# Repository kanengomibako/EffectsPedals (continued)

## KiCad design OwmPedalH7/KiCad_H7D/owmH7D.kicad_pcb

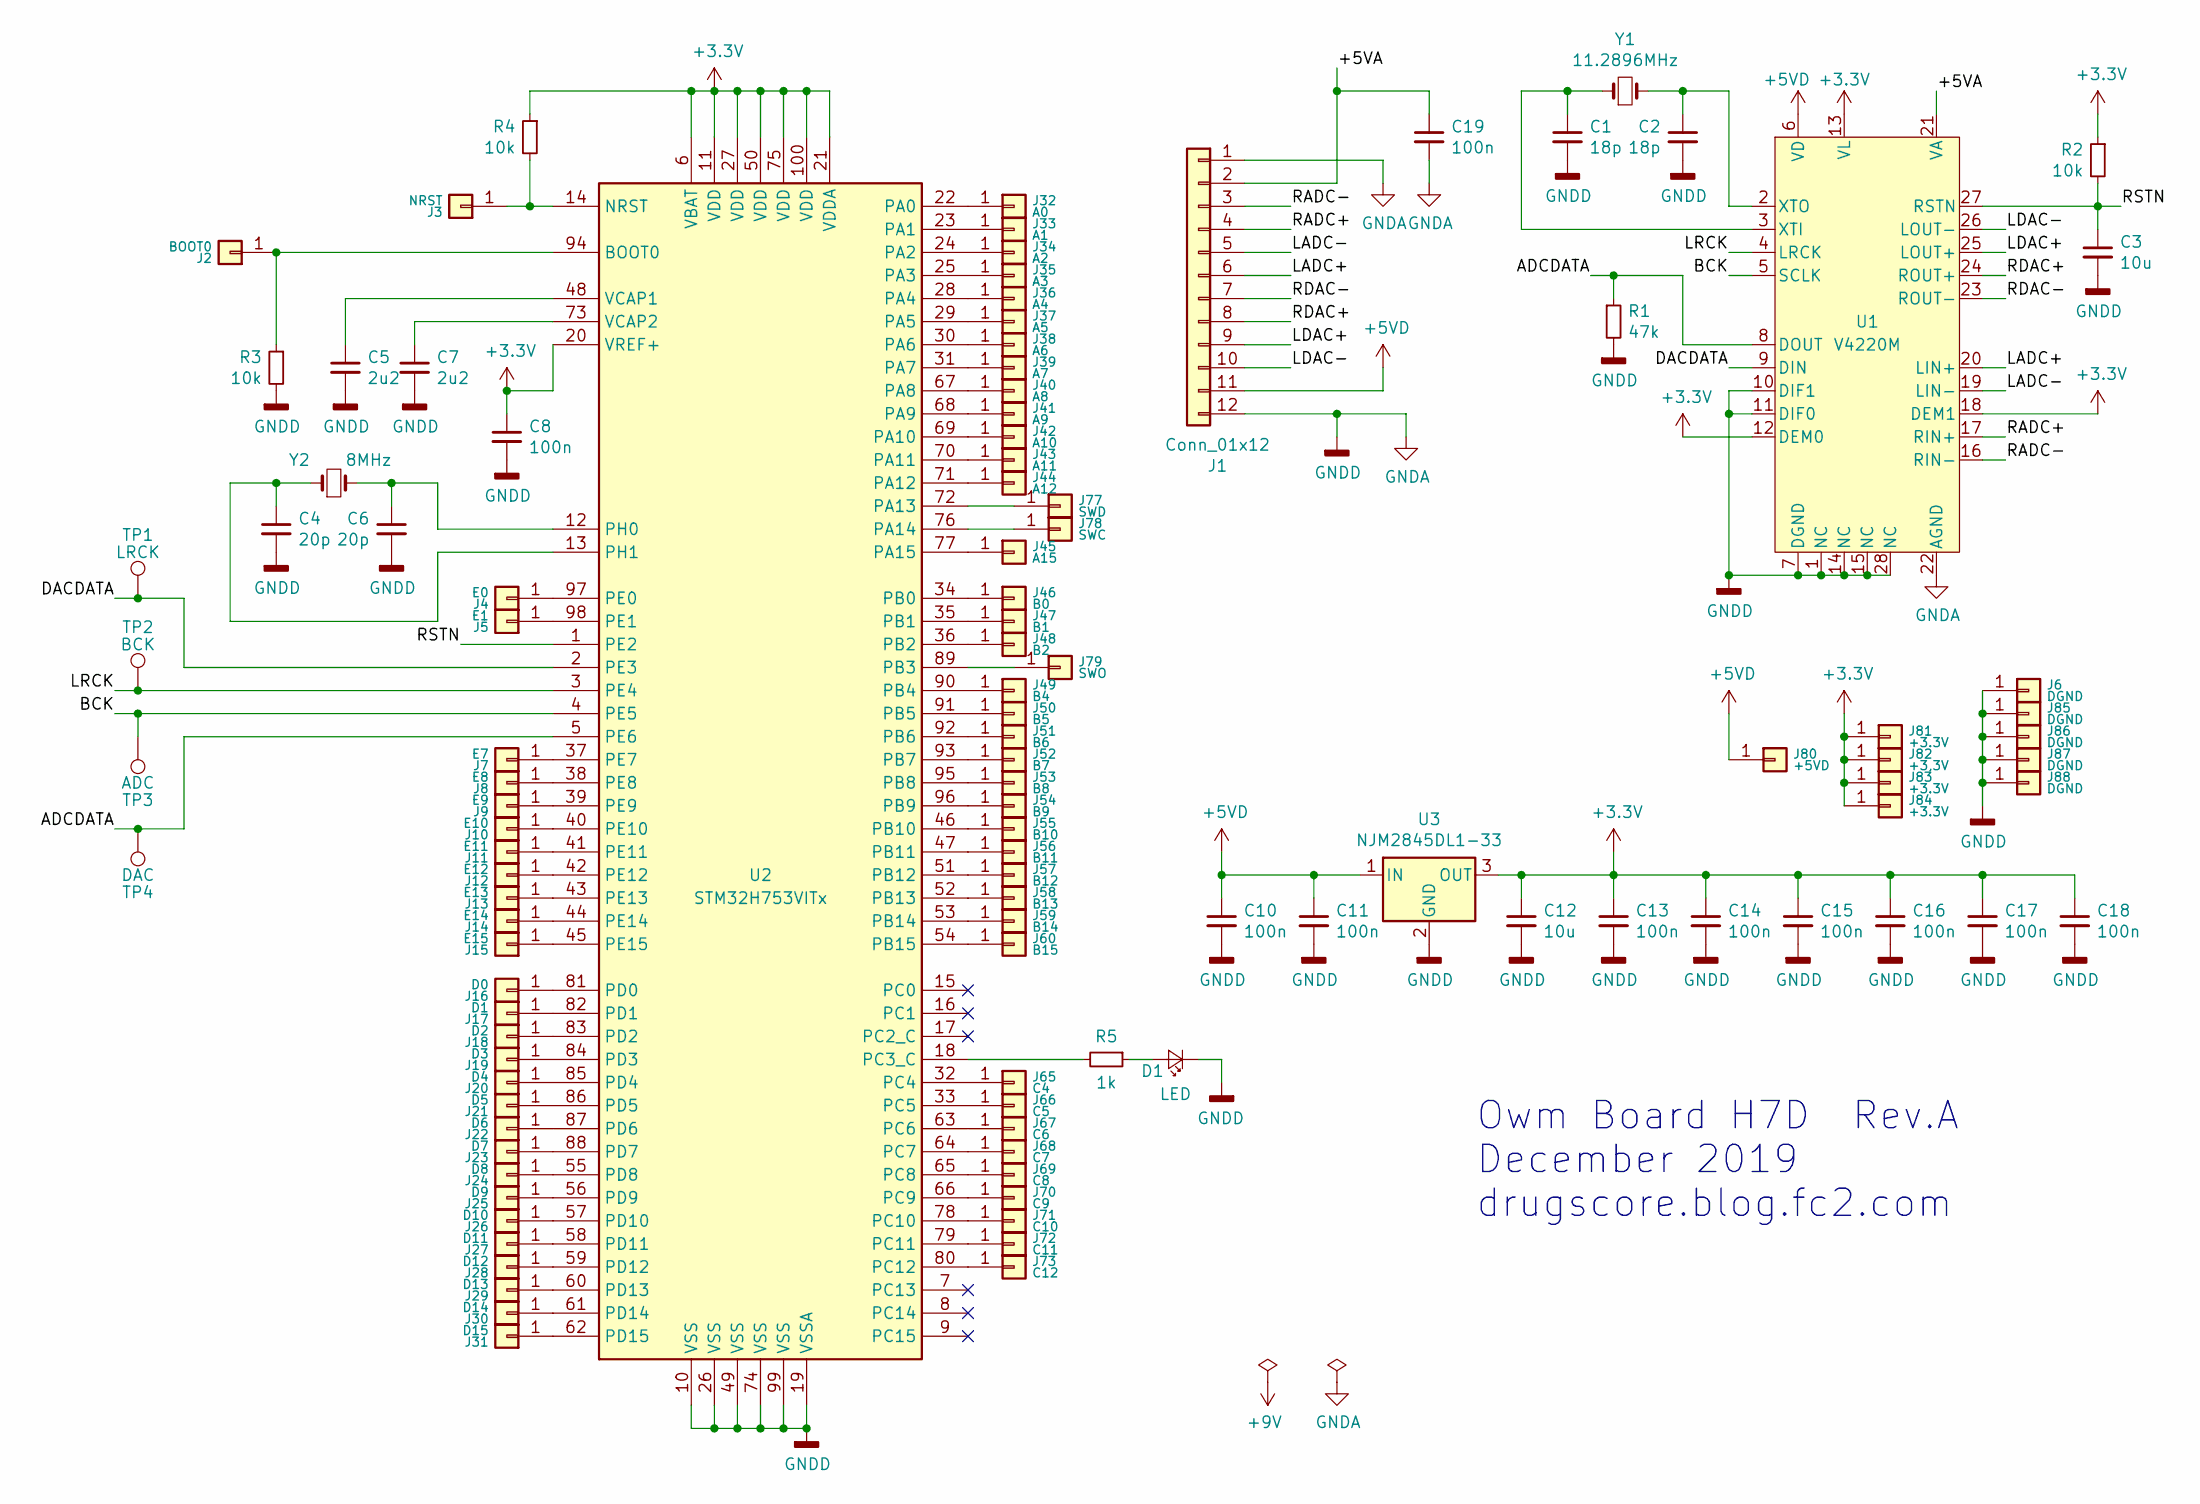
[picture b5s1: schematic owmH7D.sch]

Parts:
C1, C2: 18p; my_C_1608(0603)_HandSoldering
C3, C12: 10u; my_C_3216(1206)_HandSoldering
C4, C6: 20p; my_C_1608(0603)_HandSoldering
C5, C7: 2u2; my_C_2012(0805)_HandSoldering
C8, C10, C11, C13, C14, C15, C16, C17, C18, C19: 100n; my_C_1608(0603)_HandSoldering
D1: LED; my_R_1608(0603)_HandSoldering
J1: Conn_01x12; PinHeader_1x12_P2.54mm_Vertical
J2: BOOT0; my_SmallPad_0-8mmDrill
J3: NRST; my_SmallPad_0-8mmDrill
J4: E0; my_SmallPad_0-8mmDrill
J5: E1; my_SmallPad_0-8mmDrill
J6, J85, J86, J87, J88: DGND; my_SmallPad_0-8mmDrill
J7: E7; my_SmallestPad_0-6mmDrill
J8: E8; my_SmallestPad_0-6mmDrill
J9: E9; my_SmallestPad_0-6mmDrill
J10: E10; my_SmallestPad_0-6mmDrill
J11: E11; my_SmallestPad_0-6mmDrill
J12: E12; my_SmallestPad_0-6mmDrill
J13: E13; my_SmallestPad_0-6mmDrill
J14: E14; my_SmallestPad_0-6mmDrill
J15: E15; my_SmallestPad_0-6mmDrill
J16: D0; my_SmallestPad_0-6mmDrill
J17: D1; my_SmallestPad_0-6mmDrill
J18: D2; my_SmallestPad_0-6mmDrill
J19: D3; my_SmallestPad_0-6mmDrill
J20: D4; my_SmallestPad_0-6mmDrill
J21: D5; my_SmallestPad_0-6mmDrill
J22: D6; my_SmallestPad_0-6mmDrill
J23: D7; my_SmallestPad_0-6mmDrill
J24: D8; my_SmallPad_0-8mmDrill
J25: D9; my_SmallPad_0-8mmDrill
J26: D10; my_SmallPad_0-8mmDrill
J27: D11; my_SmallPad_0-8mmDrill
J28: D12; my_SmallPad_0-8mmDrill
J29: D13; my_SmallestPad_0-6mmDrill
J30: D14; my_SmallestPad_0-6mmDrill
J31: D15; my_SmallestPad_0-6mmDrill
J32: A0; my_SmallPad_0-8mmDrill
J33: A1; my_SmallPad_0-8mmDrill
J34: A2; my_SmallPad_0-8mmDrill
J35: A3; my_SmallPad_0-8mmDrill
J36: A4; my_SmallPad_0-8mmDrill
J37: A5; my_SmallPad_0-8mmDrill
J38: A6; my_SmallPad_0-8mmDrill
J39: A7; my_SmallPad_0-8mmDrill
J40: A8; my_SmallPad_0-8mmDrill
J41: A9; my_SmallestPad_0-6mmDrill
J42: A10; my_SmallestPad_0-6mmDrill
J43: A11; my_SmallestPad_0-6mmDrill
J44: A12; my_SmallestPad_0-6mmDrill
J45: A15; my_SmallPad_0-8mmDrill
J46: B0; my_SmallestPad_0-6mmDrill
J47: B1; my_SmallestPad_0-6mmDrill
J48: B2; my_SmallestPad_0-6mmDrill
J49: B4; my_SmallestPad_0-6mmDrill
J50: B5; my_SmallestPad_0-6mmDrill
J51: B6; my_SmallPad_0-8mmDrill
J52: B7; my_SmallPad_0-8mmDrill
J53: B8; my_SmallPad_0-8mmDrill
J54: B9; my_SmallPad_0-8mmDrill
J55: B10; my_SmallPad_0-8mmDrill
J56: B11; my_SmallPad_0-8mmDrill
J57: B12; my_SmallPad_0-8mmDrill
J58: B13; my_SmallPad_0-8mmDrill
J59: B14; my_SmallPad_0-8mmDrill
J60: B15; my_SmallPad_0-8mmDrill
J65: C4; my_SmallestPad_0-6mmDrill
J66: C5; my_SmallestPad_0-6mmDrill
J67: C6; my_SmallestPad_0-6mmDrill
J68: C7; my_SmallestPad_0-6mmDrill
J69: C8; my_SmallestPad_0-6mmDrill
J70: C9; my_SmallPad_0-8mmDrill
J71: C10; my_SmallPad_0-8mmDrill
J72: C11; my_SmallPad_0-8mmDrill
J73: C12; my_SmallPad_0-8mmDrill
J77: SWD; my_SmallPad_0-8mmDrill
J78: SWC; my_SmallPad_0-8mmDrill
J79: SWO; my_SmallPad_0-8mmDrill
J80: +5VD; my_SmallPad_0-8mmDrill
J81, J83, J84: +3.3V; my_SmallPad_0-8mmDrill
J82: +3,3V; my_SmallPad_0-8mmDrill
R1: 47k; my_R_1608(0603)_HandSoldering
R2, R3, R4: 10k; my_R_1608(0603)_HandSoldering
R5: 1k; my_R_2012(0805)_HandSoldering
TP1: LRCK; my_TestPoint_1.2mm
TP2: BCK; my_TestPoint_1.2mm
TP3: ADC; my_TestPoint_1.2mm
TP4: DAC; my_TestPoint_1.2mm
U1: V4220M; my_SSOP-28_5.3x10.2mm_Pitch0.65mm
U2: STM32H753VITx; my_LQFP-100_14x14mm_P0.5mm
U3: NJM2845DL1-33; my_TO-252-3
Y1: 11.2896MHz; Crystal_HC49-U_Vertical
Y2: 8MHz; Crystal_HC49-U_Vertical

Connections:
+3V3: C8.1, C12.1, C13.1, C14.1, C15.1, C16.1, C17.1, C18.1, J81.1, J82.1, J83.1, J84.1, R2.1, R4.1, U1.12 (DEM0), U1.13 (VL), U1.18 (DEM1), U2.6 (VBAT), U2.11 (VDD), U2.20 (VREF+), U2.21 (VDDA), U2.27 (VDD), U2.50 (VDD), U2.75 (VDD), U2.100 (VDD), U3.3 (OUT)
+5VD: C10.1, C11.1, J1.11, J80.1, U1.6 (VD), U3.1 (IN)
/+5VA: C19.1, J1.2, U1.21 (VA)
/ADCDATA: R1.1, TP4.1, U1.8 (DOUT), U2.5 (PE6)
/BCK: TP3.1, U1.5 (SCLK), U2.4 (PE5)
/DACDATA: TP1.1, U1.9 (DIN), U2.2 (PE3)
/LADC+: J1.6, U1.20 (LIN+)
/LADC-: J1.5, U1.19 (LIN-)
/LDAC+: J1.9, U1.25 (LOUT+)
/LDAC-: J1.10, U1.26 (LOUT-)
/LRCK: TP2.1, U1.4 (LRCK), U2.3 (PE4)
/RADC+: J1.4, U1.17 (RIN+)
/RADC-: J1.3, U1.16 (RIN-)
/RDAC+: J1.8, U1.24 (ROUT+)
/RDAC-: J1.7, U1.23 (ROUT-)
/RSTN: C3.1, R2.2, U1.27 (RSTN), U2.1 (PE2)
GNDA: C1.2, C2.2, C3.2, C4.2, C5.2, C6.2, C7.2, C8.2, C10.2, C11.2, C12.2, C13.2, C14.2, C15.2, C16.2, C17.2, C18.2, C19.2, D1.1 (K), J1.1, J1.12, J6.1, J85.1, J86.1, J87.1, J88.1, R1.2, R3.2, U1.1 (NC), U1.7 (DGND), U1.10 (DIF1), U1.11 (DIF0), U1.14 (NC), U1.15 (NC), U1.22 (AGND), U1.28 (NC), U2.10 (VSS), U2.19 (VSSA), U2.26 (VSS), U2.49 (VSS), U2.74 (VSS), U2.99 (VSS), U3.2 (GND)
unnamed: C1.1, U1.3 (XTI), Y1.1
unnamed: C2.1, U1.2 (XTO), Y1.2
unnamed: C4.1, U2.13 (PH1), Y2.1
unnamed: C5.1, U2.48 (VCAP1)
unnamed: C6.1, U2.12 (PH0), Y2.2
unnamed: C7.1, U2.73 (VCAP2)
unnamed: D1.2 (A), R5.1
unnamed: J2.1, R3.1, U2.94 (BOOT0)
unnamed: J3.1, R4.2, U2.14 (NRST)
unnamed: J4.1, U2.97 (PE0)
unnamed: J5.1, U2.98 (PE1)
unnamed: J7.1, U2.37 (PE7)
unnamed: J8.1, U2.38 (PE8)
unnamed: J9.1, U2.39 (PE9)
unnamed: J10.1, U2.40 (PE10)
unnamed: J11.1, U2.41 (PE11)
unnamed: J12.1, U2.42 (PE12)
unnamed: J13.1, U2.43 (PE13)
unnamed: J14.1, U2.44 (PE14)
unnamed: J15.1, U2.45 (PE15)
unnamed: J16.1, U2.81 (PD0)
unnamed: J17.1, U2.82 (PD1)
unnamed: J18.1, U2.83 (PD2)
unnamed: J19.1, U2.84 (PD3)
unnamed: J20.1, U2.85 (PD4)
unnamed: J21.1, U2.86 (PD5)
unnamed: J22.1, U2.87 (PD6)
unnamed: J23.1, U2.88 (PD7)
unnamed: J24.1, U2.55 (PD8)
unnamed: J25.1, U2.56 (PD9)
unnamed: J26.1, U2.57 (PD10)
unnamed: J27.1, U2.58 (PD11)
unnamed: J28.1, U2.59 (PD12)
unnamed: J29.1, U2.60 (PD13)
unnamed: J30.1, U2.61 (PD14)
unnamed: J31.1, U2.62 (PD15)
unnamed: J32.1, U2.22 (PA0)
unnamed: J33.1, U2.23 (PA1)
unnamed: J34.1, U2.24 (PA2)
unnamed: J35.1, U2.25 (PA3)
unnamed: J36.1, U2.28 (PA4)
unnamed: J37.1, U2.29 (PA5)
unnamed: J38.1, U2.30 (PA6)
unnamed: J39.1, U2.31 (PA7)
unnamed: J40.1, U2.67 (PA8)
unnamed: J41.1, U2.68 (PA9)
unnamed: J42.1, U2.69 (PA10)
unnamed: J43.1, U2.70 (PA11)
unnamed: J44.1, U2.71 (PA12)
unnamed: J45.1, U2.77 (PA15)
unnamed: J46.1, U2.34 (PB0)
unnamed: J47.1, U2.35 (PB1)
unnamed: J48.1, U2.36 (PB2)
unnamed: J49.1, U2.90 (PB4)
unnamed: J50.1, U2.91 (PB5)
unnamed: J51.1, U2.92 (PB6)
unnamed: J52.1, U2.93 (PB7)
unnamed: J53.1, U2.95 (PB8)
unnamed: J54.1, U2.96 (PB9)
unnamed: J55.1, U2.46 (PB10)
unnamed: J56.1, U2.47 (PB11)
unnamed: J57.1, U2.51 (PB12)
unnamed: J58.1, U2.52 (PB13)
unnamed: J59.1, U2.53 (PB14)
unnamed: J60.1, U2.54 (PB15)
unnamed: J65.1, U2.32 (PC4)
unnamed: J66.1, U2.33 (PC5)
unnamed: J67.1, U2.63 (PC6)
unnamed: J68.1, U2.64 (PC7)
unnamed: J69.1, U2.65 (PC8)
unnamed: J70.1, U2.66 (PC9)
unnamed: J71.1, U2.78 (PC10)
unnamed: J72.1, U2.79 (PC11)
unnamed: J73.1, U2.80 (PC12)
unnamed: J77.1, U2.72 (PA13)
unnamed: J78.1, U2.76 (PA14)
unnamed: J79.1, U2.89 (PB3)
unnamed: R5.2, U2.18 (PC3_C)

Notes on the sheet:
Owm Board H7D Rev.A December 2019 drugscore.blog.fc2.com

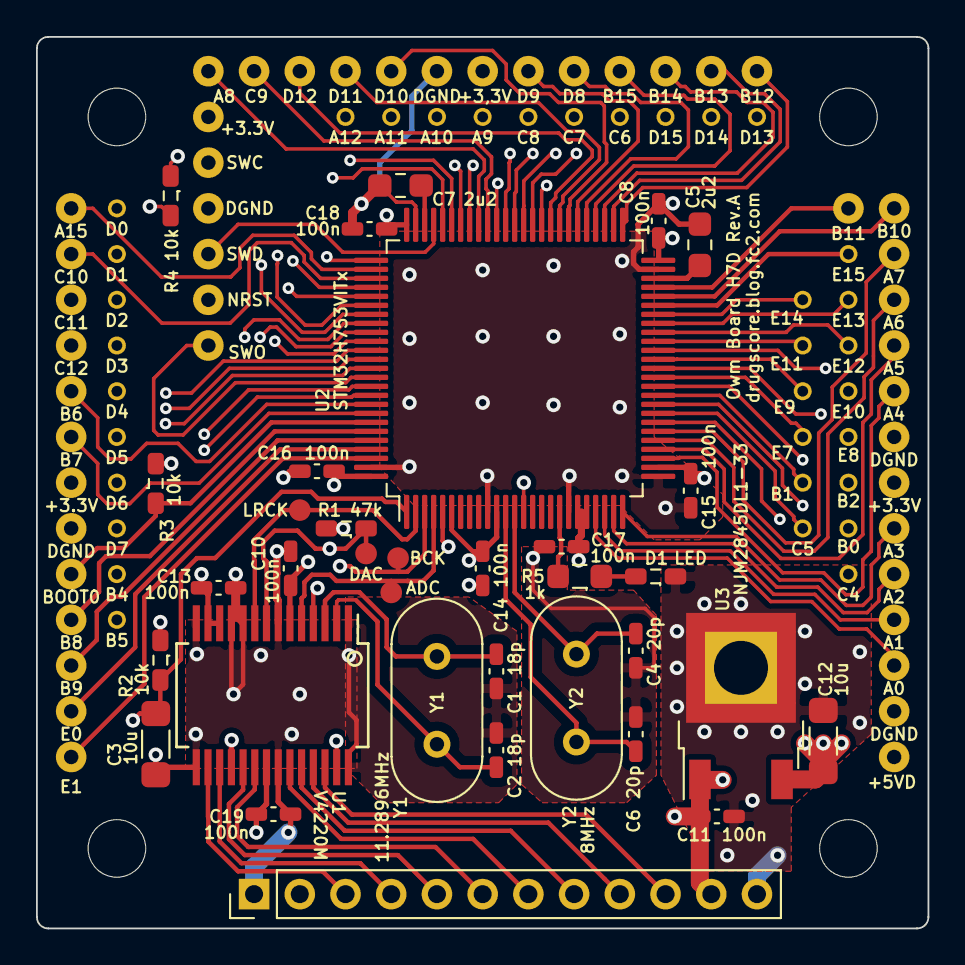
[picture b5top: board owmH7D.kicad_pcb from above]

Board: 4 copper layers, 49.5 x 49.5 mm, 114 parts (0 on the bottom side), 95 nets.
